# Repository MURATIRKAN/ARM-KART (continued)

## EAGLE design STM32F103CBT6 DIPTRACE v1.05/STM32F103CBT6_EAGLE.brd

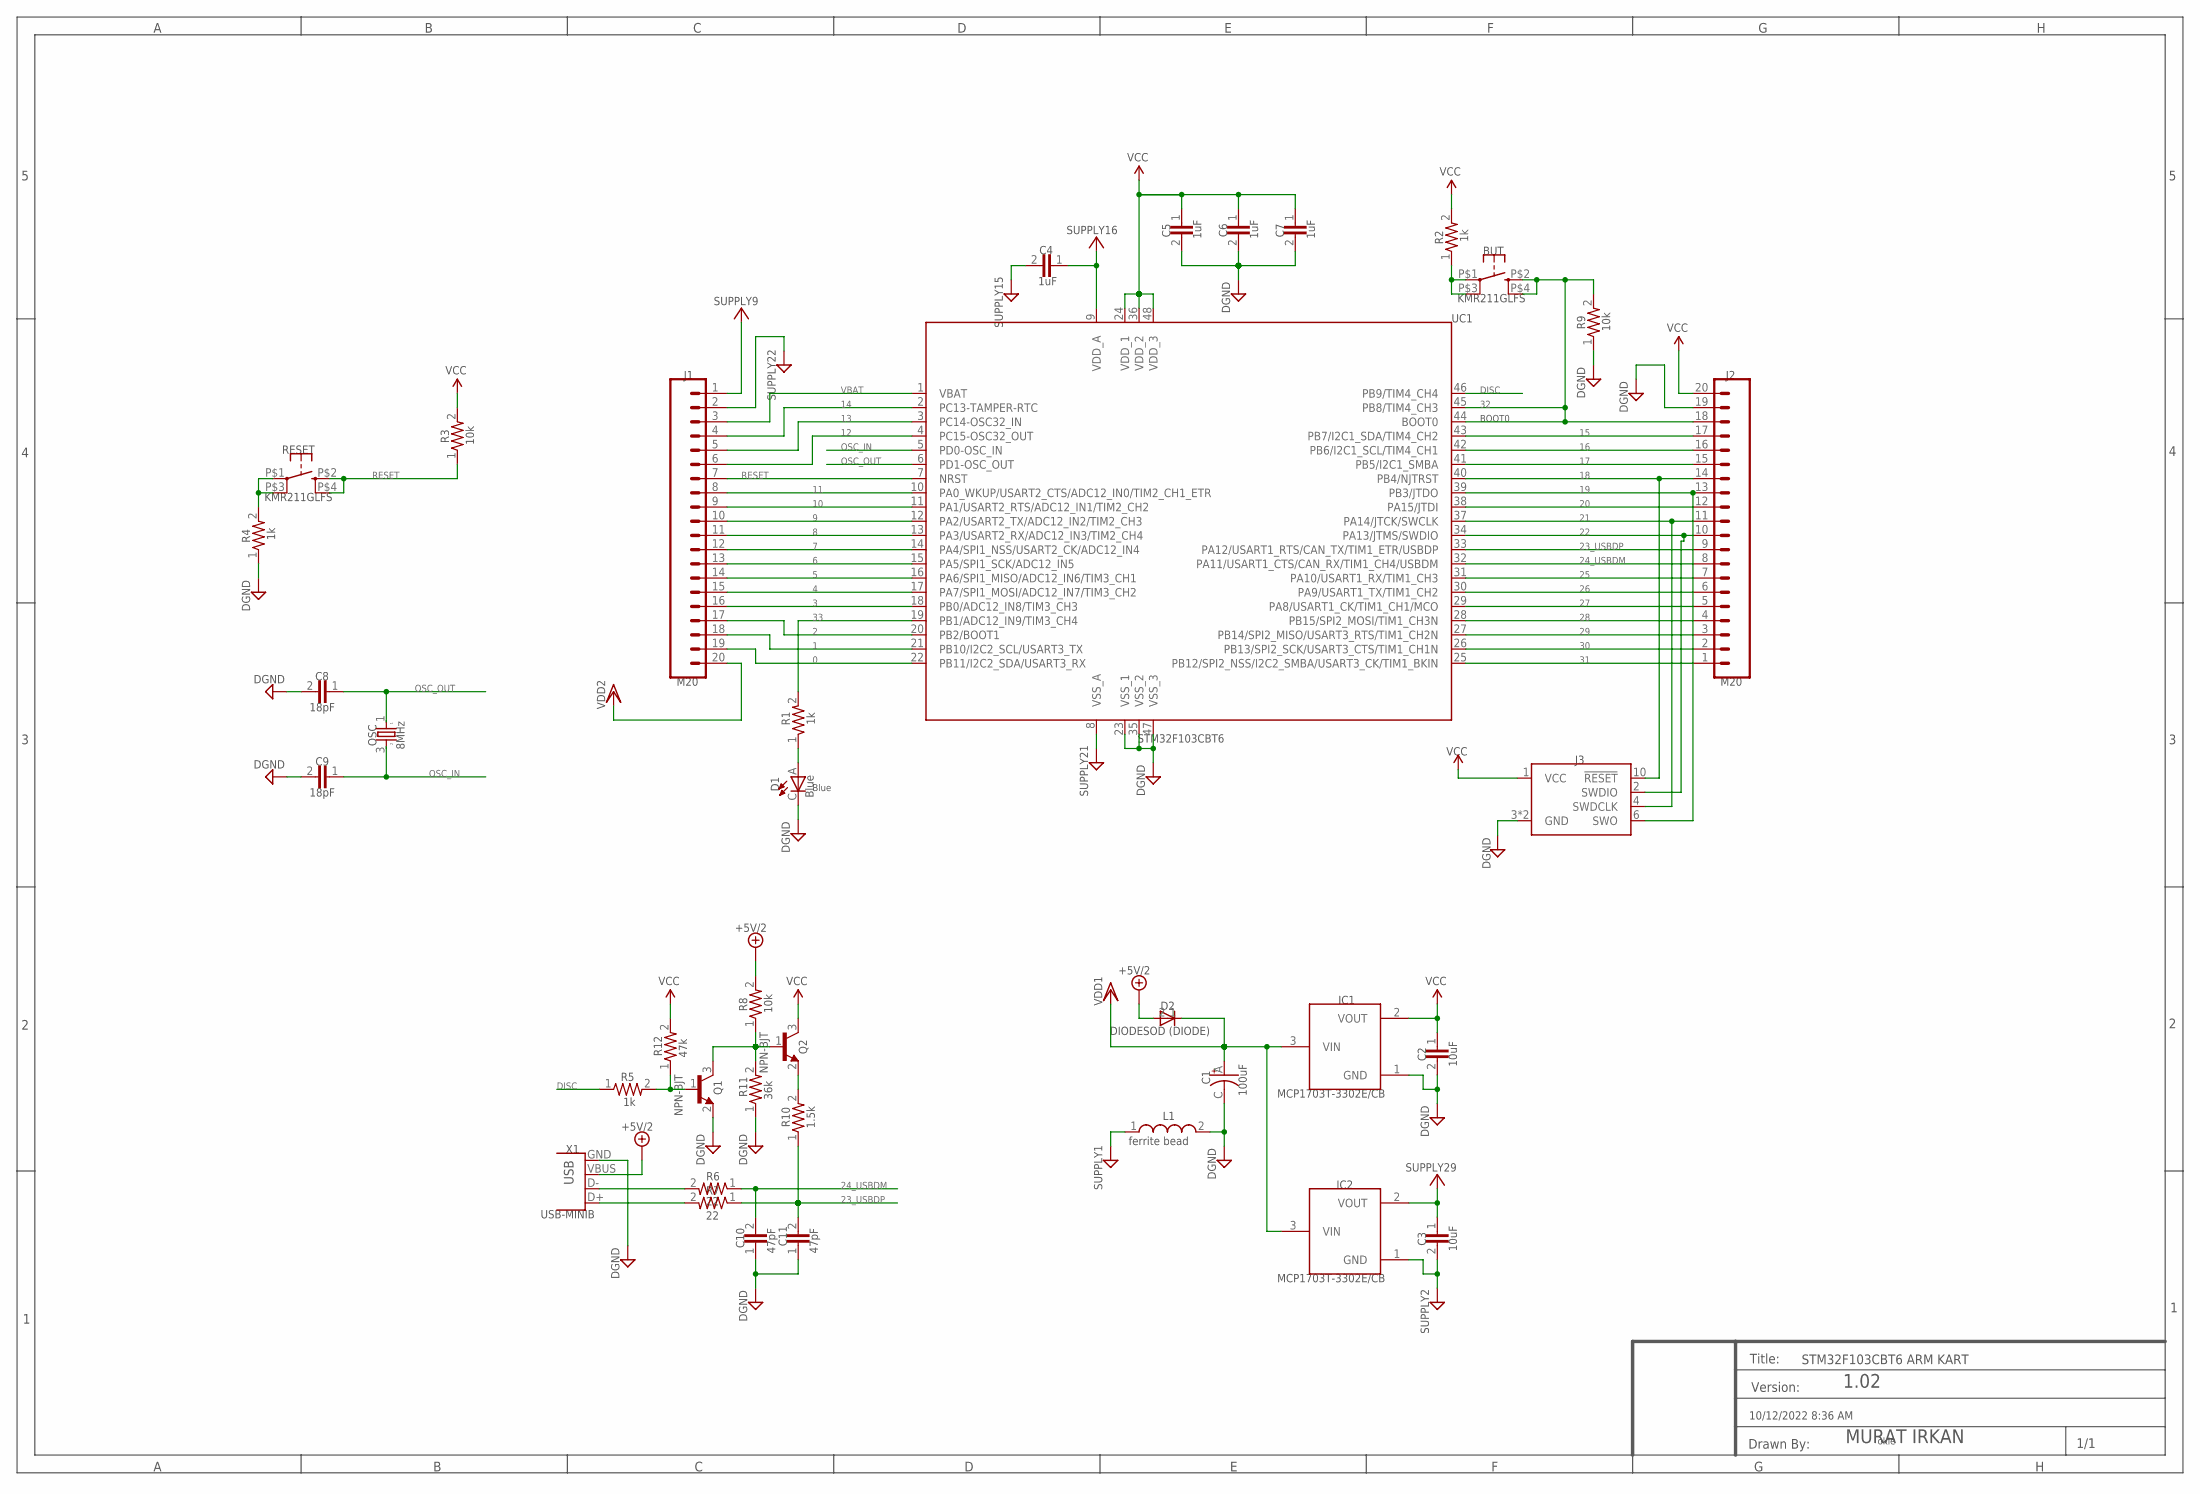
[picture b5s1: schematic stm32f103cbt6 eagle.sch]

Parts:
BUT: KMR211GLFS; PUSHBUTTON-KMR241GLFS
C1: 100uF; EIA3216
C2, C3: 10uF; 0805
C4, C5, C6, C7: 1uF; C0402
C8, C9: 18pF; C0402
C10, C11: 47pF; C0402
D1: Blue; LED-1206
D2: DIODESOD_(DIODE); SOD-323
IC1, IC2: MCP1703T-3302E/CB; SOT23
J1, J2: M20; 1X20
J3: CORTEX_DEBUG; 2X5-PTH-1.27MM-NO_SILK
L1: ferrite bead; 0603
OSC: 8MHz; CRYSTAL-SMD-5X3
Q1, Q2: NPN-BJT; SOT23_21
R1, R2, R4, R5: 1k; C0402
R3, R8, R9: 10k; C0402
R6, R7: 22; C0402
R10: 1.5k; C0402
R11: 36k; C0402
R12: 47k; C0402
RESET: KMR211GLFS; PUSHBUTTON-KMR241GLFS
UC1: STM32F103CBT6; LQFP48
X1: USB-MINIB

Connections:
0: J1.19, UC1.22 (PB11/I2C2_SDA/USART3_RX)
1: J1.18, UC1.21 (PB10/I2C2_SCL/USART3_TX)
2: J1.17, UC1.20 (PB2/BOOT1)
3: J1.16, UC1.18 (PB0/ADC12_IN8/TIM3_CH3)
4: J1.15, UC1.17 (PA7/SPI1_MOSI/ADC12_IN7/TIM3_CH2)
5: J1.14, UC1.16 (PA6/SPI1_MISO/ADC12_IN6/TIM3_CH1)
6: J1.13, UC1.15 (PA5/SPI1_SCK/ADC12_IN5)
7: J1.12, UC1.14 (PA4/SPI1_NSS/USART2_CK/ADC12_IN4)
8: J1.11, UC1.13 (PA3/USART2_RX/ADC12_IN3/TIM2_CH4)
9: J1.10, UC1.12 (PA2/USART2_TX/ADC12_IN2/TIM2_CH3)
10: J1.9, UC1.11 (PA1/USART2_RTS/ADC12_IN1/TIM2_CH2)
11: J1.8, UC1.10 (PA0_WKUP/USART2_CTS/ADC12_IN0/TIM2_CH1_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)
12: J1.6, UC1.4 (PC15-OSC32_OUT)
13: J1.5, UC1.3 (PC14-OSC32_IN)
14: J1.4, UC1.2 (PC13-TAMPER-RTC)
15: J2.17, UC1.43 (PB7/I2C1_SDA/TIM4_CH2)
16: J2.16, UC1.42 (PB6/I2C1_SCL/TIM4_CH1)
17: J2.15, UC1.41 (PB5/I2C1_SMBA)
18: J2.14, J3.10 (!RESET), UC1.40 (PB4/NJTRST)
19: J2.13, J3.6 (SWO), UC1.39 (PB3/JTDO)
20: J2.12, UC1.38 (PA15/JTDI)
21: J2.11, J3.4 (SWDCLK), UC1.37 (PA14/JTCK/SWCLK)
22: J2.10, J3.2 (SWDIO), UC1.34 (PA13/JTMS/SWDIO)
23_USBDP: C11.2, J2.9, R7.1, R10.1, UC1.33 (PA12/USART1_RTS/CAN_TX/TIM1_ETR/USBDP)
24_USBDM: C10.2, J2.8, R6.1, UC1.32 (PA11/USART1_CTS/CAN_RX/TIM1_CH4/USBDM)
25: J2.7, UC1.31 (PA10/USART1_RX/TIM1_CH3)
26: J2.6, UC1.30 (PA9/USART1_TX/TIM1_CH2)
27: J2.5, UC1.29 (PA8/USART1_CK/TIM1_CH1/MCO)
28: J2.4, UC1.28 (PB15/SPI2_MOSI/TIM1_CH3N)
29: J2.3, UC1.27 (PB14/SPI2_MISO/USART3_RTS/TIM1_CH2N)
30: J2.2, UC1.26 (PB13/SPI2_SCK/USART3_CTS/TIM1_CH1N)
31: J2.1, UC1.25 (PB12/SPI2_NSS/I2C2_SMBA/USART3_CK/TIM1_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)
32: BUT.P$2 (2), BUT.P$4 (4), J2.18, R9.2, UC1.44 (BOOT0), UC1.45 (PB8/TIM4_CH3)
33: R1.2, UC1.19 (PB1/ADC12_IN9/TIM3_CH4)
+5V/2: D2.2 (A), R8.2, X1.VBUS
AV+: C3.1, C4.1, IC2.2 (VOUT), J1.1, UC1.9 (VDD_A); also elsewhere on the board
AV-: C3.2, C4.2, IC2.1 (GND), J1.2, L1.1, UC1.8 (VSS_A)
DGND: C1.C (-), C2.2, C5.2, C6.2, C7.2, C8.2, C9.2, C10.1, C11.1, D1.C, IC1.1 (GND), J2.19, J3.3 (GND), J3.5 (GND), J3.9, L1.2, Q1.2 (E), R4.1, R9.1, R11.1, UC1.23 (VSS_1), UC1.35 (VSS_2), UC1.47 (VSS_3), X1.GND; also elsewhere on the board
DISC: R5.1, UC1.46 (PB9/TIM4_CH4)
unnamed: D1.A, R1.1
unnamed: R4.2, RESET.P$1 (1), RESET.P$3 (3)
unnamed: Q2.2 (E), R10.2
unnamed: R6.2, X1.D-
unnamed: R7.2, X1.D+
unnamed: Q1.3 (C), Q2.1 (B), R8.1, R11.2
unnamed: Q1.1 (B), R5.2, R12.1
OSC_IN: C9.1, OSC.3 (2), UC1.5 (PD0-OSC_IN)
OSC_OUT: C8.1, OSC.1, UC1.6 (PD1-OSC_OUT)
RESET: J1.7, R3.1, RESET.P$2 (2), RESET.P$4 (4), UC1.7 (NRST)
VBAT: J1.3, UC1.1 (VBAT)
VCC: C2.1, C5.1, C6.1, C7.1, IC1.2 (VOUT), J2.20, J3.1 (VCC), Q2.3 (C), R2.2, R3.2, R12.2, UC1.24 (VDD_1), UC1.36 (VDD_2), UC1.48 (VDD_3); also elsewhere on the board
VIN: C1.A (+), D2.1 (C), IC1.3 (VIN), IC2.3 (VIN), J1.20

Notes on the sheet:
1.02
okie
BOOT0
Blue
STM32F103CBT6 ARM KART
10/12/2022 8:36 AM
1/1
Drawn By:
Title:
Version:
MURAT IRKAN
BUT
KMR211GLFS
100uF
10uF
1uF
18pF
C10
47pF
C11
DIODESOD (DIODE)
IC1
MCP1703T-3302E/CB
IC2
M20
ferrite bead
OSC
8MHz
VCC
NPN-BJT
10k
R10
1.5k
R11
36k
R12
47k
RESET
SUPPLY1
SUPPLY2

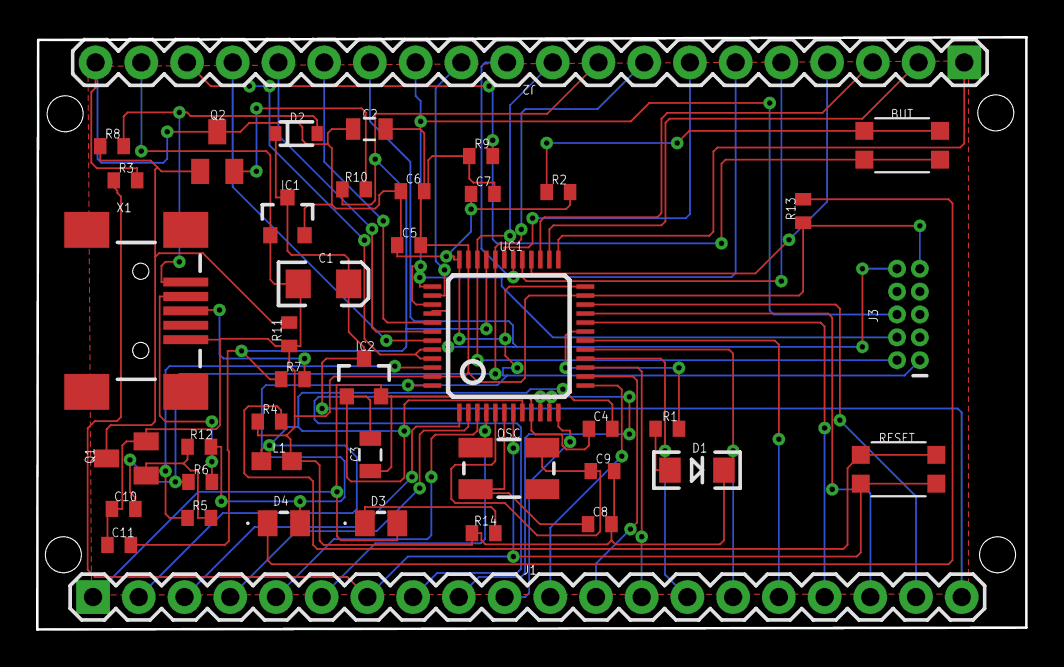
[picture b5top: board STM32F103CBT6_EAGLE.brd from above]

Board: 2 copper layers, 55.0 x 32.9 mm, 42 parts (0 on the bottom side), 54 nets.

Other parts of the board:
D3: 598-8191-107F; LEDC2012X70N
D4: 598-8170-107F; LEDC2012X70N
R13, R14: 330; C0402

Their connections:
AV+: D3.A; also elsewhere on the board
DGND: R13.1, R14.1; also elsewhere on the board
Net_53: D4.C, R13.2
Net_55: D3.C, R14.2
VCC: D4.A; also elsewhere on the board

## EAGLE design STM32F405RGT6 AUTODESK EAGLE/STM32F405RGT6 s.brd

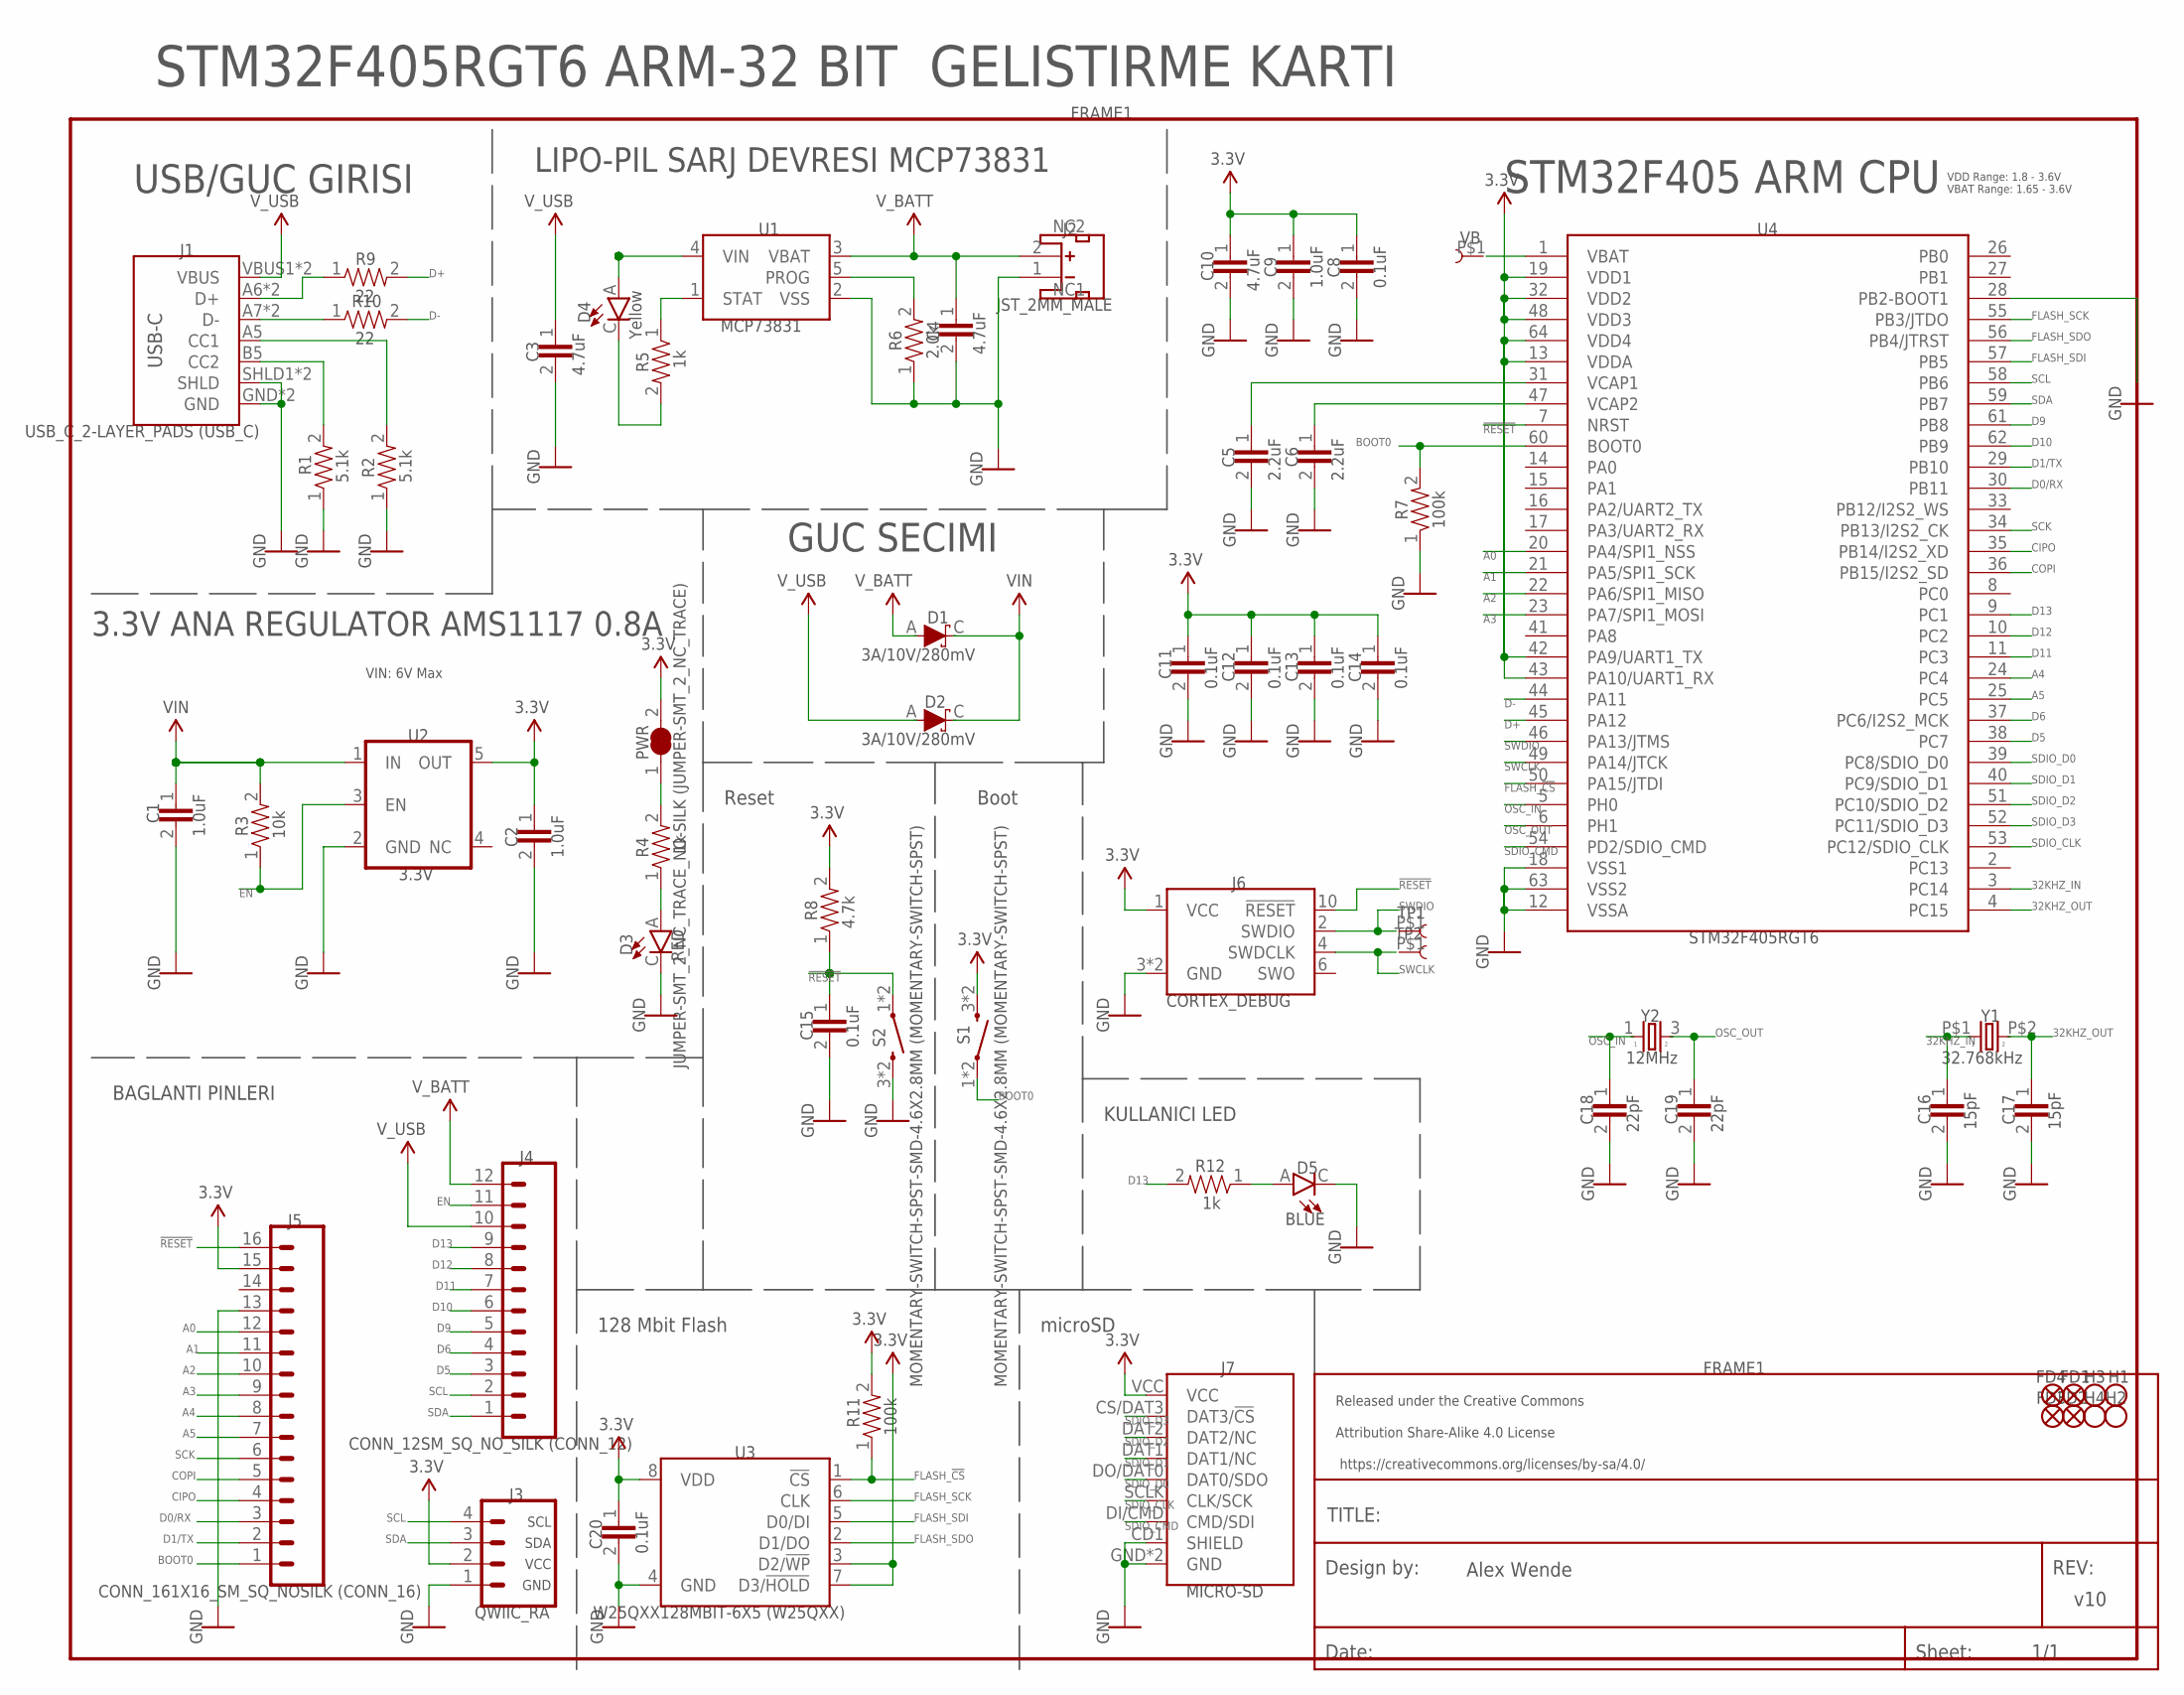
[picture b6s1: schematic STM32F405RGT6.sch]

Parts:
C1, C2, C9: 1.0uF; 0402-TIGHT
C3, C4, C10: 4.7uF; 0402-TIGHT
C5, C6: 2.2uF; 0402-TIGHT
C8, C11, C12, C13, C14, C15, C20: 0.1uF; 0402-TIGHT
C16, C17: 15pF; 0402-TIGHT
C18, C19: 22pF; 0402-TIGHT
D1, D2: 3A/10V/280mV; SOD-323
D3: RED; LED-0603
D4: Yellow; LED-0603
D5: BLUE; LED-0603
FD1, FD2, FD3, FD4: FIDUCIALUFIDUCIAL_(FIDUCIAL); FIDUCIAL-MICRO
FRAME1: FRAME-LETTER; CREATIVE_COMMONS
H1, H2, H3, H4: STAND-OFFTIGHT_(STAND-OFF); STAND-OFF-TIGHT
J1: USB_C_2-LAYER_PADS_(USB_C); USB-C-16P-2LAYER-PADS
J2: JST_2MM_MALE; JST-2-SMD
J3: QWIIC_RA; JST04_1MM_RA
J4: CONN_12SM_SQ_NO_SILK_(CONN_12); 1X12_SM_SQ_NOSILK
J5: CONN_161X16_SM_SQ_NOSILK_(CONN_16); 1X16_SM_SQ_NOSILK
J6: CORTEX_DEBUG; 2X5-PTH-1.27MM-NO_SILK
J7: MICRO-SD; MICRO-SD-SOCKET
PWR: JUMPER-SMT_2_NC_TRACE_NO-SILK_(JUMPER-SMT_2_NC_TR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; SMT-JUMPER_2_NC_TRACE_NO-SILK
R1, R2: 5.1k; 0603
R3: 10k; 0603
R4, R5, R12: 1k; 0402-TIGHT
R6: 2.0k; 0603
R7, R11: 100k; 0402-TIGHT
R8: 4.7k; 0603
R9, R10: 22; 0603
S1, S2: MOMENTARY-SWITCH-SPST-SMD-4.6X2.8MM_(MOMENTARY-SW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; TACTILE_SWITCH_SMD_4.6X2.8MM
TP1, TP2: TEST-POINT3_(TEST-POINT); PAD.03X.03
U1: MCP73831; SOT23-5
U2: 3.3V; SOT23-5
U3: W25QXX128MBIT-6X5_(W25QXX); WSON-8-6X5
U4: STM32F405RGT6; TQFP64
VB: TEST-POINT3_(TEST-POINT); PAD.03X.03
Y1: 32.768kHz; CRYSTAL-SMD-3.2X1.5MM
Y2: 12MHz; CRYSTAL-SMD-5X3.2-4PAD

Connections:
3.3V: C2.1, C8.1, C9.1, C10.1, C11.1, C12.1, C13.1, C14.1, C20.1, J3.2, J5.15, J6.1 (VCC), J7.VCC, PWR.2, R8.2, R11.2, S1.3 (2), S1.4 (2), U2.5 (OUT), U3.3 (D2/!WP!), U3.7 (D3/!HOLD!), U3.8 (VDD), U4.13 (VDDA), U4.19 (VDD1), U4.32 (VDD2), U4.42 (PA9/UART1_TX), U4.43 (PA10/UART1_RX), U4.48 (VDD3), U4.64 (VDD4)
32KHZ_IN: C16.1, U4.3 (PC14), Y1.P$1 (1)
32KHZ_OUT: C17.1, U4.4 (PC15), Y1.P$2 (2)
!RESET: C15.1, J5.16, J6.10 (!RESET), R8.1, S2.1, S2.2 (1), U4.7 (NRST)
A0: J5.12, U4.20 (PA4/SPI1_NSS)
A1: J5.11, U4.21 (PA5/SPI1_SCK)
A2: J5.10, U4.22 (PA6/SPI1_MISO)
A3: J5.9, U4.23 (PA7/SPI1_MOSI)
A4: J5.8, U4.24 (PC4)
A5: J5.7, U4.25 (PC5)
BOOT0: J5.1, R7.2, S1.1, S1.2 (1), U4.60 (BOOT0)
CIPO: J5.4, U4.35 (PB14/I2S2_XD)
COPI: J5.5, U4.36 (PB15/I2S2_SD)
D0/RX: J5.3, U4.30 (PB11)
D1/TX: J5.2, U4.29 (PB10)
D5: J4.3, U4.38 (PC7)
D6: J4.4, U4.37 (PC6/I2S2_MCK)
D9: J4.5, U4.61 (PB8)
D10: J4.6, U4.62 (PB9)
D11: J4.7, U4.11 (PC3)
D12: J4.8, U4.10 (PC2)
D13: J4.9, R12.2, U4.9 (PC1)
D+: R9.2, U4.45 (PA12)
D-: R10.2, U4.44 (PA11)
EN: J4.11, R3.1, U2.3 (EN)
FLASH_!CS: R11.1, U3.1 (!CS!), U4.50 (PA15/JTDI)
FLASH_SCK: U3.6 (CLK), U4.55 (PB3/JTDO)
FLASH_SDI: U3.5 (D0/DI), U4.57 (PB5)
FLASH_SDO: U3.2 (D1/DO), U4.56 (PB4/JTRST)
GND: C1.2, C2.2, C3.2, C4.2, C5.2, C6.2, C8.2, C9.2, C10.2, C11.2, C12.2, C13.2, C14.2, C15.2, C16.2, C17.2, C18.2, C19.2, C20.2, D3.C, D5.C, J1.GND, J1.GND2 (GND), J1.SHLD1 (SHLD), J1.SHLD2 (SHLD), J1.SHLD3, J1.SHLD4, J2.1 (-), J3.1, J5.13, J6.3 (GND), J6.5 (GND), J6.9, J7.CD1 (SHIELD), J7.GND, J7.GND1 (GND), J7.GND3, R1.1, R2.1, R6.1, R7.1, S2.3 (2), S2.4 (2), U1.2 (VSS), U2.2 (GND), U3.4 (GND), U4.12 (VSSA), U4.18 (VSS1), U4.28 (PB2-BOOT1), U4.63 (VSS2)
unnamed: D5.A, R12.1
unnamed: PWR.1, R4.2
unnamed: J1.A6 (D+), J1.B6 (D+), R9.1
unnamed: J1.A7 (D-), J1.B7 (D-), R10.1
unnamed: D3.A, R4.1
unnamed: R6.2, U1.5 (PROG)
unnamed: J1.A5 (CC1), R2.2
unnamed: J1.B5 (CC2), R1.2
unnamed: D4.C, R5.2
unnamed: R5.1, U1.1 (STAT)
unnamed: C5.1, U4.31 (VCAP1)
unnamed: C6.1, U4.47 (VCAP2)
OSC_IN: C18.1, U4.5 (PH0), Y2.1
OSC_OUT: C19.1, U4.6 (PH1), Y2.3 (2)
SCK: J5.6, U4.34 (PB13/I2S2_CK)
SCL: J3.4, J4.2, U4.58 (PB6)
SDA: J3.3, J4.1, U4.59 (PB7)
SDIO_CLK: J7.SCLK (CLK/SCK), U4.53 (PC12/SDIO_CLK)
SDIO_CMD: J7.DI/CMD (CMD/SDI), U4.54 (PD2/SDIO_CMD)
SDIO_D0: J7.DO/DAT0 (DAT0/SDO), U4.39 (PC8/SDIO_D0)
SDIO_D1: J7.DAT1 (DAT1/NC), U4.40 (PC9/SDIO_D1)
SDIO_D2: J7.DAT2 (DAT2/NC), U4.51 (PC10/SDIO_D2)
SDIO_D3: J7.CS/DAT3 (DAT3/!CS!), U4.52 (PC11/SDIO_D3)
SWCLK: J6.4 (SWDCLK), TP2.P$1, U4.49 (PA14/JTCK)
SWDIO: J6.2 (SWDIO), TP1.P$1, U4.46 (PA13/JTMS)
VB: U4.1 (VBAT), VB.P$1
VIN: C1.1, D1.C, D2.C, R3.2, U2.1 (IN)
V_BATT: C4.1, D1.A, J2.2 (+), J4.12, U1.3 (VBAT)
V_USB: C3.1, D2.A, D4.A, J1.VBUS1 (VBUS), J1.VBUS2 (VBUS), J4.10, U1.4 (VIN)

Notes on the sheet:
v10
Alex Wende
3.3V ANA REGULATOR AMS1117 0.8A
VIN: 6V Max
LIPO-PIL SARJ DEVRESI MCP73831
USB/GUC GIRISI
GUC SECIMI
BAGLANTI PINLERI
microSD
128 Mbit Flash
Reset
Boot
KULLANICI LED
VDD Range: 1.8 - 3.6V VBAT Range: 1.65 - 3.6V
STM32F405 ARM CPU
STM32F405RGT6 ARM-32 BIT GELISTIRME KARTI
FRAME1
Date:
Sheet:
1/1
REV:
TITLE:
Released under the Creative Commons
Attribution Share-Alike 4.0 License
https://creativecommons.org/licenses/by-sa/4.0/
Design by:
STM32F405RGT6
USB-C
USB_C_2-LAYER_PADS (USB_C)
5.1k
RED
GND
3.3V
1.0uF
VIN
10k
3A/10V/280mV
V_BATT
V_USB
JST_2MM_MALE

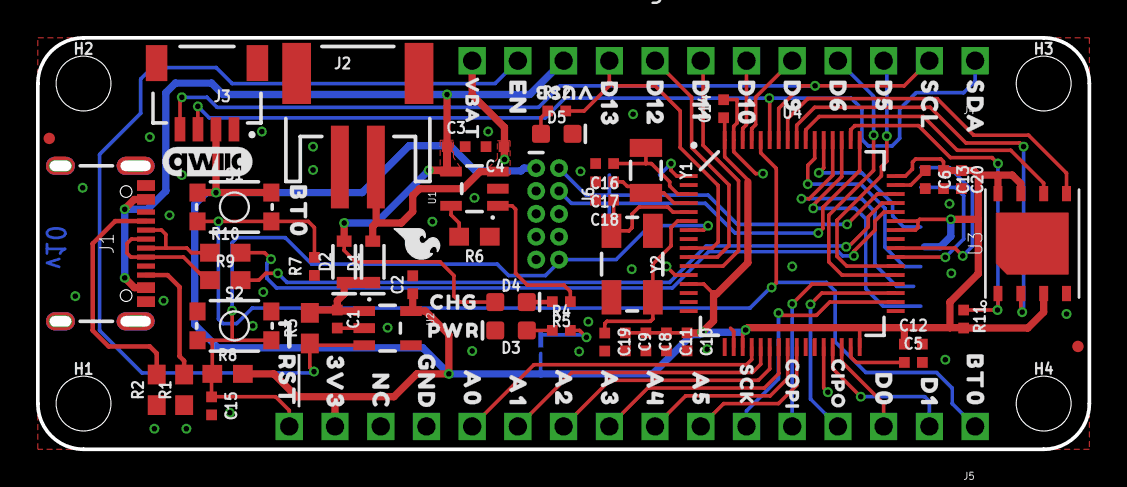
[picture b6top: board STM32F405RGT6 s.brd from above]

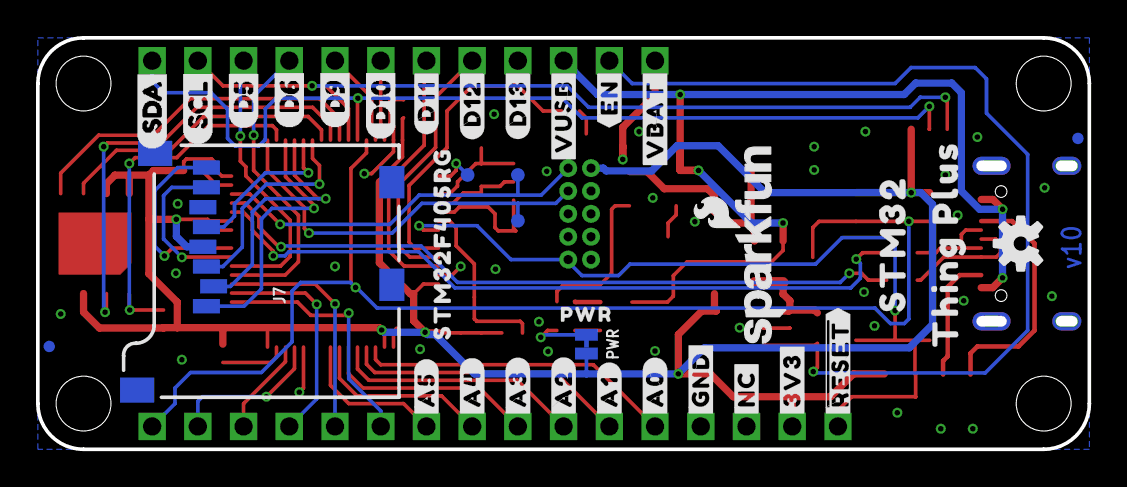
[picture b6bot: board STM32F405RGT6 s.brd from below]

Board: 2 copper layers, 58.4 x 22.9 mm, 124 parts (35 on the bottom side), 59 nets.

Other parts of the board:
LOGO1: QWIIC_LOGO_5MM; QWIIC_5MM
LOGO2: SFE_LOGO_NAME_FLAME.1_INCH; SFE_LOGO_NAME_FLAME_.1
LOGO3: OSHW-LOGOS; OSHW-LOGO-S
U$1: D53
U$2: #RST#0
U$3, U$49: BT00
U$4: D130
U$5, U$58: PWR0
U$6: CHG0
U$7: ##RESET##0
U$8: #3V3#0
U$9: #NC#0
U$10: #GND#0
U$11: #A0#0
U$12: #A1#0
U$13: #A2#0
U$14: #A3#0
U$15: #A4#0
U$16: #A5#0
U$23: D62
U$24: D91
U$25, U$55: D100
U$26: SCL4
U$27: SDA5
U$29: #D11#0
U$30: #D12#0
U$31: #D13#0
U$32: #VUSB#0
U$33: #EN#0
U$34: #VBAT#0
U$35: 3V30
U$36: NC0
U$37: GND0
U$38: A00
U$39: A10
U$40: A20
U$41: A30
U$42: A40
U$43: A50
U$44: SCK0
U$45: COPI0
U$46: CIPO0
U$47: D00
U$48: D10
U$50: VBAT_0
U$51: EN_0
U$52: D50
U$53: D60
U$54: D90
U$56: D110
U$57: D120
U$59: SCL_0
U$60: SDA_0
U$61: VUSB0
U$62: STM320
U$63: THING_PLUS0
U$64: STM32F405RG0
U$65: SFE_LOGO_FLAME_.1
